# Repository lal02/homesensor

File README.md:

# homesensor

## Description
This project, which is built around the esp32 microcontroller, started out as a simple [Spring Application](https://github.com/lal02/Centralized-Web-Application) while I was doing an internship as a part of my university's practical semester. 
The goal of the Spring Application was to get familiar with Spring in general.

The Spring application mentioned above has additional features that are not relevant to the homesensor setup and will therefore not be discussed in this repository.

The idea was to use the esp32 as a data source to get some hands-on experience with REST interfaces and Data Handling in Spring. 
Beyond just being a learning exercise, this project turned out to be really useful. 
By collecting and graphing temperature data, I was able to spot a problem with the underfloor heating in my apartment.

The esp32 collects data from a variety of sensors and transmits it to the Spring backend through REST interfaces. 
The Spring backend, in turn, offers multiple REST interfaces for both sending and retrieving data. 
Additionally, a Raspberry Pi controls a 64x64 LED matrix, which displays data received from the Spring backend. 
It also adjusts the brightness of the LED matrix based on the light intensity data obtained.

## Overview
This sketch illustrates the structure of all the hardware and software components, as well as how they interact with each other.

<br> </br>

## Esp32 and Sensor Integration
The project commenced as a modest undertaking, utilising an ESP32 microcontroller and a DHT22 sensor to gather and transmit temperature and humidity data. 
Subsequent to this, the setup was expanded by the addition of further sensors, including the TSL2561 for the purpose of measuring light intensity, and subsequently the MQ7 and MQ135 for the purpose of measuring air quality. 
In order to enhance the ease of use, a number of quality-of-life features have been incorporated. 
These included an LCD screen that displayed the IP address and the time until the next sensor reading. 
Furthermore, an HTTP server was configured on the ESP32, incorporating two endpoints. 
The primary endpoint facilitates the retrieval of hardware-related information in the form of an HTML file, encompassing details such as the IP address, MAC address, host name, WiFi SSID, and the list of connected sensors along with their respective functions. 
In conclusion, a touch button was incorporated, the actuation of which initiates a sensor reading.
Presently, both the ESP32 and the sensors are stored within a cardboard box. 
This short term storage method will be replaced in the future by a custom 3D printed case.

## Raspberry Pi no.1 
The system is constructed around a Raspberry Pi 3, which hosts a variety of essential services. 
The system operates a Tomcat service, which contains a Spring application, thereby providing a robust backend for the management of a variety of tasks. 
Furthermore, the Raspberry Pi is equipped with a GitHub Actions runner, thereby enabling DevOps processes and continuous integration/continuous deployment (CI/CD) pipelines. 
It also manages a PostgreSQL database, thereby enabling efficient data storage and management.
It is evident that when a multitude of applications are operating concurrently, the Raspberry Pi 3 reaches its maximum performance capacity. 
During periods of substantial data loading, such as retrieving large amounts of data via a REST Interface Call, the system encounters performance bottlenecks. 
This performance limitation suggests that, in the future, it might be beneficial to transfer these operations to a machine with greater computing power to ensure smoother and more efficient processing.

## Raspberry Pi no.2
The Raspberry Pi is programmed to execute a Python script that enables the control of a connected 64x64 LED matrix. 
However, it should be noted that due to the utilisation of Python bindings, the performance is less than optimal which causes visible flickers caused by low Hz. 
The present script has been developed for interaction with the REST interface of a Spring application, with a view to both the display of data and the regulation of the brightness of the LED matrix. 
This objective is realised through the retrieval of the most recent light intensity data, which is then utilised to adjust the brightness. 
Furthermore, the script utilises the API of OpenWeatherMap to retrieve current weather information, thereby integrating external data into the display system.

<br> </br>

## PCB
With the help of a friend I managed to design a pcb using KiCad and ordered it from pcbway.
The PCB-Design is very basic and still has room for improvement. 
This is an area where I had no previous experience in and I learned a lot from tinkering around with KiCad.

## Learnings
Throughout this project, I've gained a variety of skills and knowledge. 
This includes for example soldering and electronics, which were essential for building and troubleshooting hardware. 
I learned about the I2C protocol for device communication and improved my ability to read datasheets for component specifications. 
My Linux skills advanced, particularly in system configuration and hardware interaction. 
Additionally, I developed an understanding of hardware requirements, such as program storage size and computational power for running httpservers.

# Potential Upgrades
In the future, there are a number of potential enhancements that could be made to this project. 
A notable enhancement would be Over-the-Air (OTA) updates on the esp32. 
This feature facilitates seamless, wireless updates to the system, thereby ensuring that upgrades and maintenance can be effortlessly executed without the necessity for physical access to the device.
Furthermore, the utilisation of the available C++ bindings for the LED matrix is another possibility..
This would enhance performance and efficiency by leveraging the capabilities of C++, which has been demonstrated to offer superior resource management and faster execution compared to Python.

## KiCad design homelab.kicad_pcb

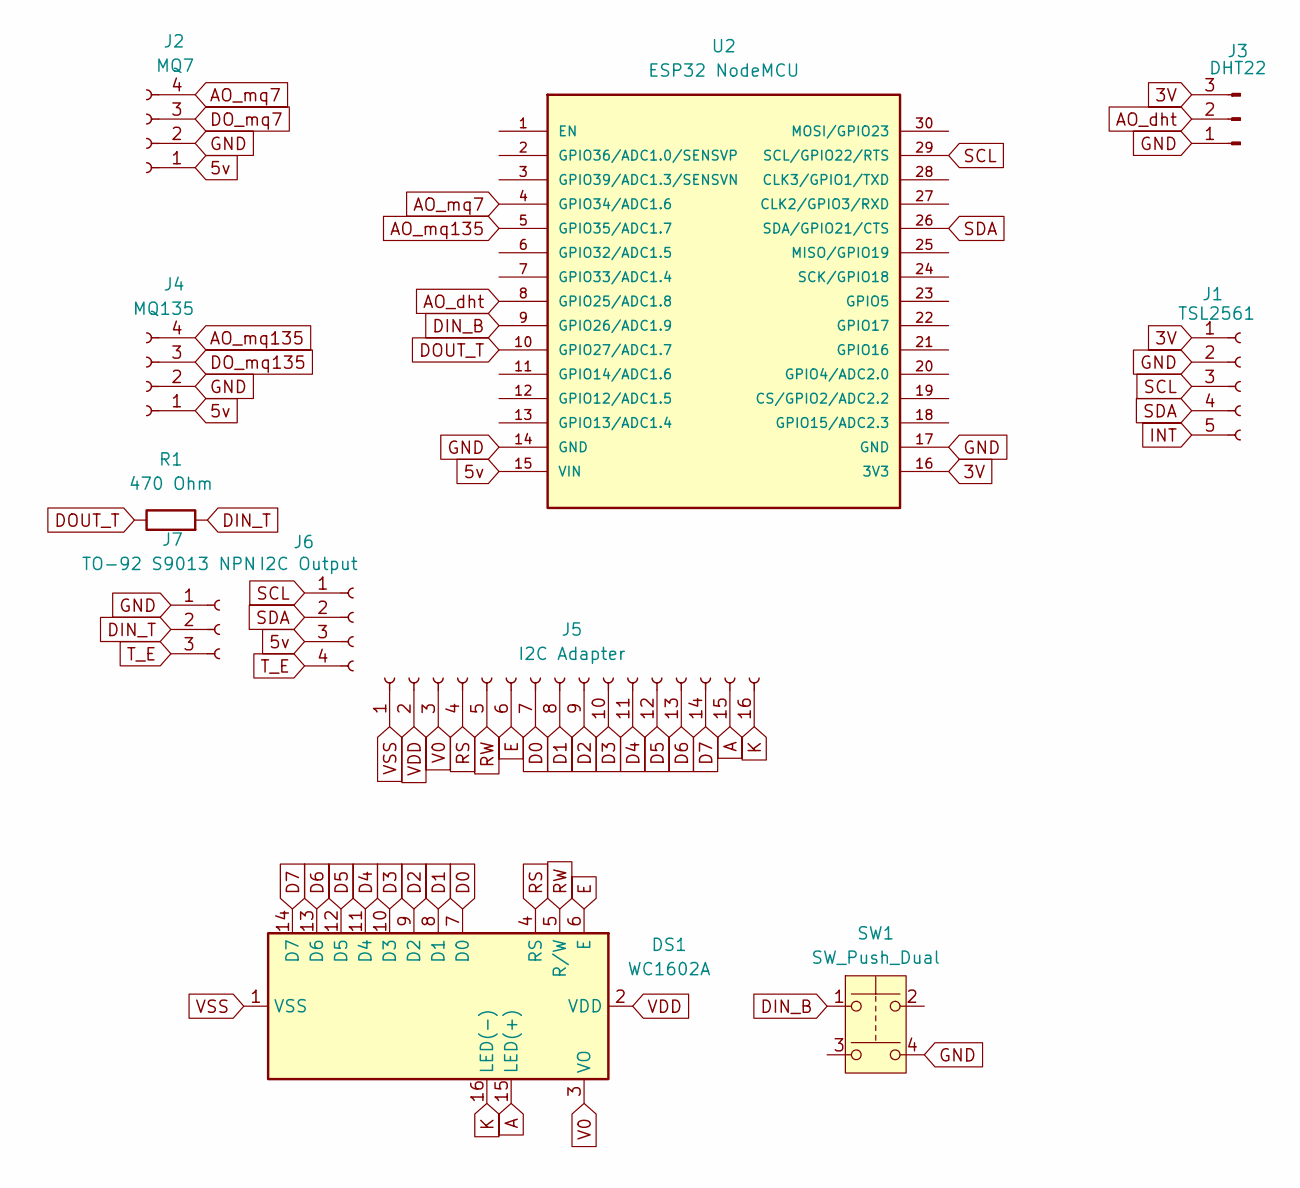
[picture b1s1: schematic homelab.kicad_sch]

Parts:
DS1: WC1602A
J1: TSL2561; PinSocket_1x05_P2.54mm_Vertical
J2: MQ7; PinSocket_1x04_P2.54mm_Horizontal
J3: DHT22; PinHeader_1x03_P2.54mm_Vertical
J4: MQ135; PinSocket_1x04_P2.54mm_Horizontal
J5: I2C Adapter; PinSocket_1x16_P2.54mm_Vertical
J6: I2C Output; PinHeader_1x04_P2.54mm_Vertical
J7: TO-92 S9013 NPN; PinSocket_1x03_P2.54mm_Vertical
R1: 470 Ohm; R_Axial_DIN0204_L3.6mm_D1.6mm_P1.90mm_Vertical
SW1: SW_Push_Dual; SW_PUSH_6mm
U2: ESP32 NodeMCU; ESP32-C3-DevKitM-1; PARTREV 23/04/2025

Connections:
3V: J1.1, J3.3, U2.16 (3V3)
5v: J2.1, J4.1, J6.3, U2.15 (VIN)
A: DS1.15 (LED(+)), J5.15
AO_dht: J3.2, U2.8 (GPIO25/ADC1.8)
AO_mq7: J2.4, U2.4 (GPIO34/ADC1.6)
AO_mq135: J4.4, U2.5 (GPIO35/ADC1.7)
D0: DS1.7 (D0), J5.7
D1: DS1.8 (D1), J5.8
D2: DS1.9 (D2), J5.9
D3: DS1.10 (D3), J5.10
D4: DS1.11 (D4), J5.11
D5: DS1.12 (D5), J5.12
D6: DS1.13 (D6), J5.13
D7: DS1.14 (D7), J5.14
DIN_B: SW1.1, U2.9 (GPIO26/ADC1.9)
DIN_T: J7.2, R1.2
DOUT_T: R1.1, U2.10 (GPIO27/ADC1.7)
DO_mq7: J2.3
DO_mq135: J4.3
E: DS1.6 (E), J5.6
GND: J1.2, J2.2, J3.1, J4.2, J7.1, SW1.4, U2.14 (GND), U2.17 (GND)
INT: J1.5
K: DS1.16 (LED(-)), J5.16
RS: DS1.4 (RS), J5.4
RW: DS1.5 (R/W), J5.5
SCL: J1.3, J6.1, U2.29 (SCL/GPIO22/RTS)
SDA: J1.4, J6.2, U2.26 (SDA/GPIO21/CTS)
T_E: J6.4, J7.3
V0: DS1.3 (VO), J5.3
VDD: DS1.2 (VDD), J5.2
VSS: DS1.1 (VSS), J5.1

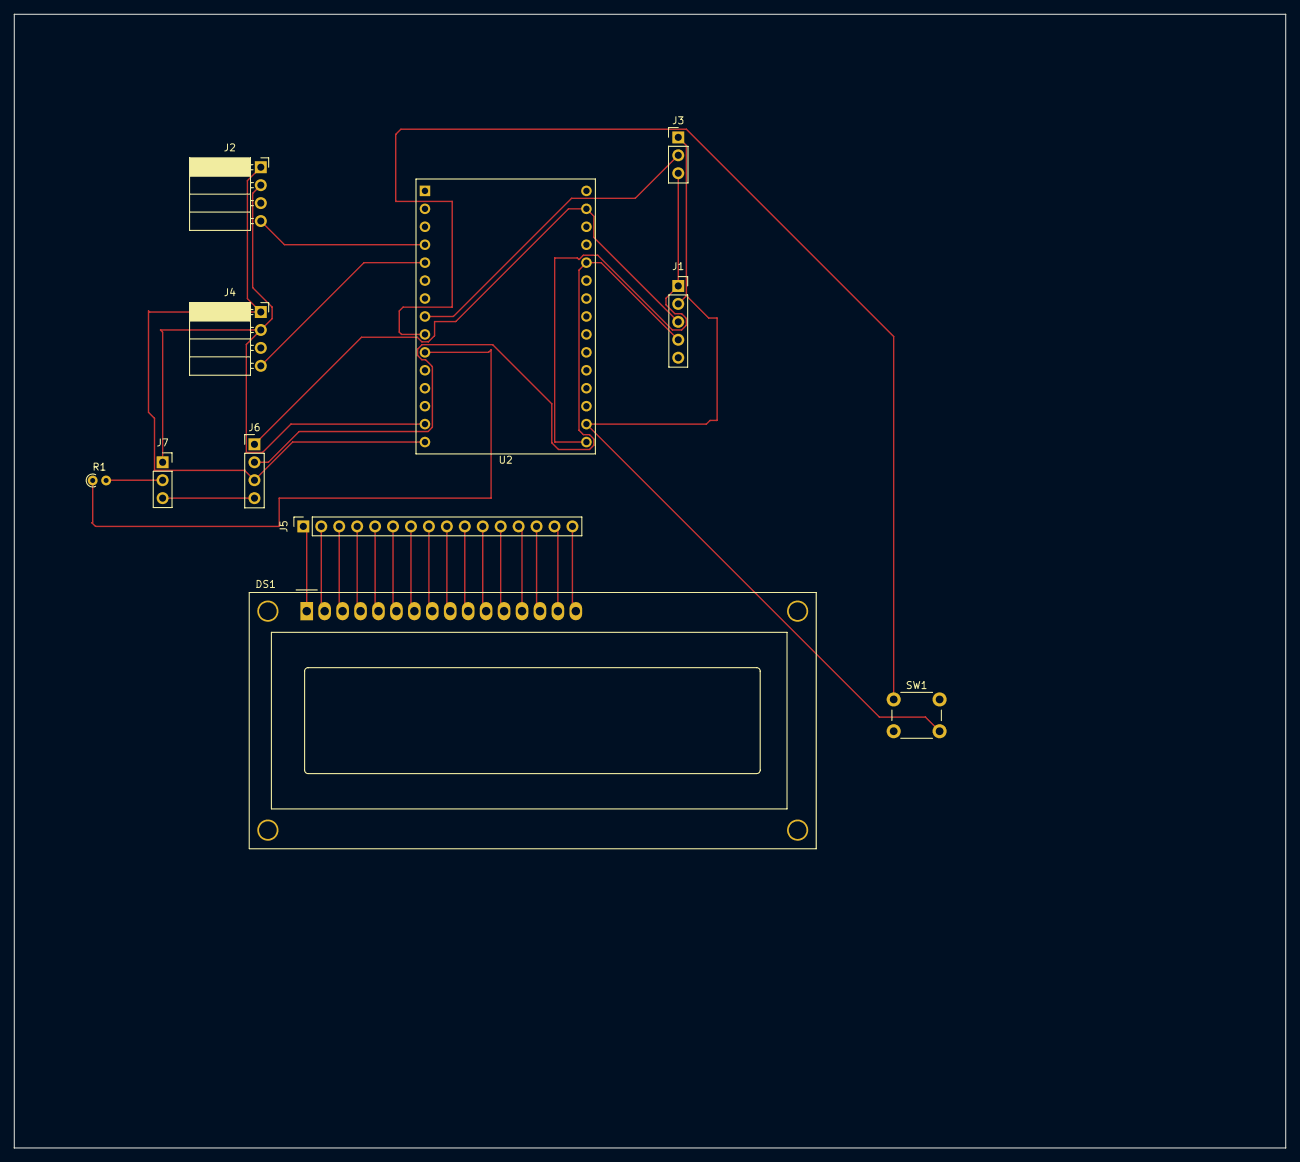
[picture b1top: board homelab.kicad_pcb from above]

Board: 2 copper layers, 180.0 x 160.5 mm, 11 parts (0 on the bottom side), 28 nets.

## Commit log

2025-08-04 updated version to current state
2025-08-17 PCB Backup
2025-09-04 remove obsolete files
2025-09-29 Update README.md, added pcb description
